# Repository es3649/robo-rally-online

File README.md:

# RoboRally Online

editing on windows now

RoboRally Online is a Typescript/robotics implementation of the RoboRally board game, by Richard Garfield and Renegade Game Studio.

One day, while playing RoboRally, I thought to myself, _"How cool would it be if the robots on the board were actual robots, and I could actually program them?"_ so I decided to make it for real.
I started with a high-school physics knowledge of electronics, then read forums, watched videos, and bothered friends until I was able to figure out how to make it work.
This repository contains a majority of the files and code needed to bring the project to life.

**Disclaimer**: This project is not affiliated with nor endorsed by Richard Garfield nor Renegade Game Studio

## Contents

* [Contents](#contents)
* [Setup Instructions](#setup-instructions)
* [Project Structure](#project-structure)
    * [Player Client](#player-client)
    * [Host Application](#host-application)
    * [Bot Drivers](#bot-drivers)
    * [Schematics](#schematics)

## Setup Instructions

This project is the fullest stack application&mdash;all it's missing is a database.
Instructions for setting up a game (assuming the code is installed, running, and the bots are assembled) can be found in [playing.md](./doc/playing.md).
More comprehensive setup instructions, including instructions for setting up the execution environment and assembling bots, are provided in [setup.md](./doc/setup.md).

## Project Structure

The project is broken into 4 main parts:

* Player Client
* Host Application
* Bot Drivers
* Schematics

### Player Client

The Player Client, contained in the `player-client` directory, is a Vue+Vite+Pinia web application which provides a web interface for playing the game

### Host Application

The host application, in the `robo-rally-host` folder, is an Electron+Vite+Vue3 desktop application written in Typescript which provides an interface for starting the game, choosing some game settings, and managing Bluetooth connections with the robots.
It also contains a express-powered and socket.io-enabled server for hosting and joining games, and for handling communication with the players.
This server serves the Player Client.

### Bot Drivers

The bot drivers, in the `bot-drivers` directory, are a series of Arduino programs, designed to control robots over a Bluetooth connection managed by the host.

### Schematics

The `schematics` folder contains PCB and CAD schematics.

The PCB schematics are created using KiCad to model the custom boards used inside each robot.
For simplicity, there is one schematic to service all bots, and thus all robot features will be supported on each PCB.
Robots which do not support a certain feature, will simply have relevant components omitted, and will not have those components supported in their drivers.

CAD schematics are created in OnShape, and contain the 3D models for the robots.
Each of these is unique.

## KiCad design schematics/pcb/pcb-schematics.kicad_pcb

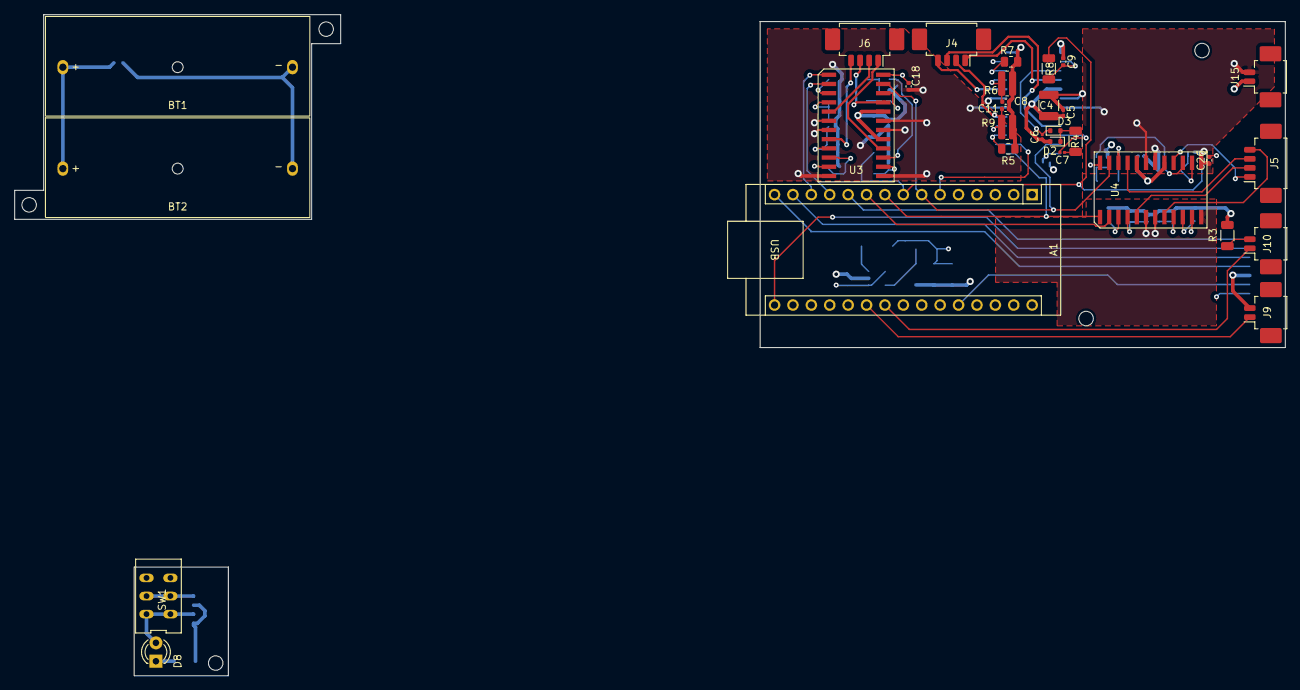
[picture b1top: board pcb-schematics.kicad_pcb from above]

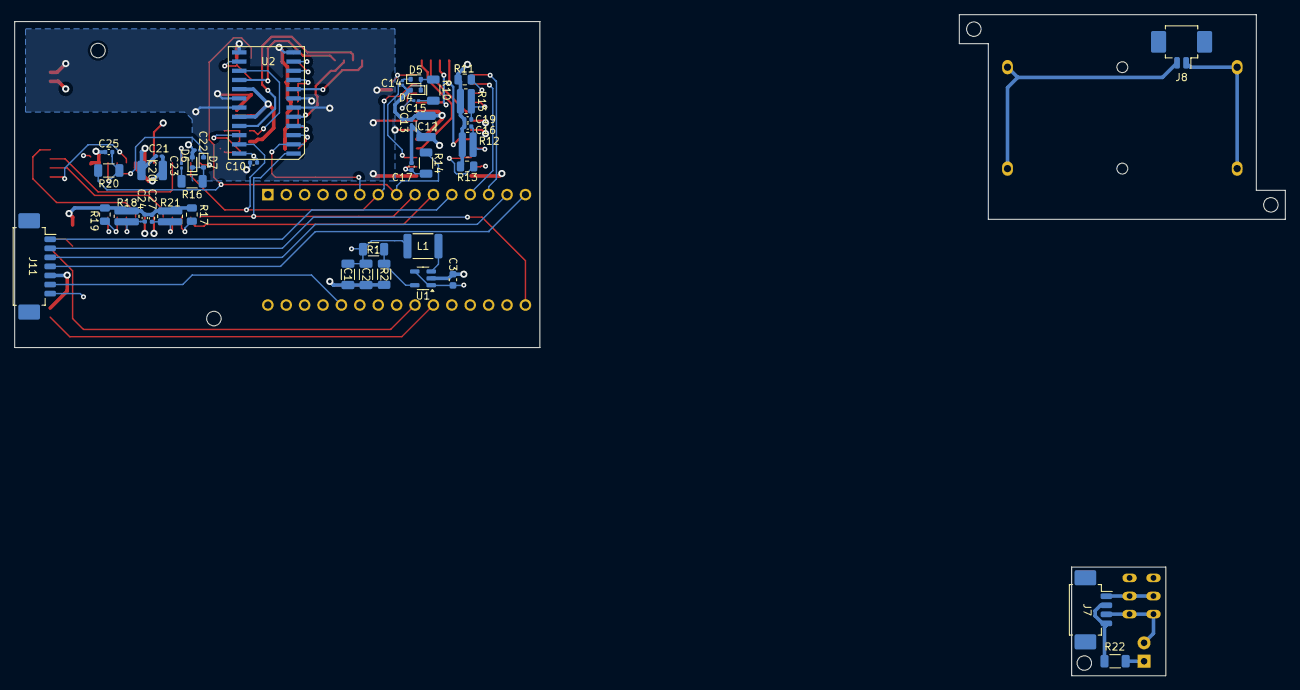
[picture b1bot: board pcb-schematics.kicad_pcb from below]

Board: 4 copper layers, 175.4 x 91.2 mm, 74 parts (43 on the bottom side), 66 nets.

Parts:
A1: Arduino_Nano_33_BLE; Arduino_Nano
BT1, BT2: Battery; Battery_clip-MPD_BHA23APC
C1, C2: 22uF; C_1206_3216Metric
C3: 4.7uF; C_0603_1608Metric
C4, C12, C20: 100uF; C_1210_3225Metric
C5, C13, C21: 0.1uF; C_0201_0603Metric_Pad0.64x0.40mm_HandSolder
C6, C14, C22: 0.22uF; C_0201_0603Metric
C7, C15, C23: 0.01uF; C_0201_0603Metric
C8, C11, C16, C19, C24, C27: 1000pF; C_0402_1005Metric
C9, C17, C25: 5600pF; C_0402_1005Metric
C10, C18, C26: 0.068uF; C_0402_1005Metric
D2, D3, D4, D5, D6, D7: 1N4148; D_SOD-523
D8: LED; LED_D3.0mm
J4, J5, J6, J7: Conn_01x04_Socket; Molex_PicoBlade_53261-0471_1x04-1MP_P1.25mm_Horizontal
J8, J9, J10, J15: Conn_01x02_Socket; Molex_PicoBlade_53261-0271_1x02-1MP_P1.25mm_Horizontal
J11: Conn_01x07_Socket; Molex_PicoBlade_53261-0771_1x07-1MP_P1.25mm_Horizontal
L1: 2.2uH; L_1812_4532Metric
R1, R8, R14, R20, R22: 100K; R_1206_3216Metric
R2: 200K; R_1206_3216Metric
R3, R4, R10, R16: 100; R_1206_3216Metric
R5, R6, R11, R12, R17, R18: 0.3; R_0805_2012Metric
R7, R9, R13, R15, R19, R21: 39K; R_0612_1632Metric
SW1: SW_DPDT_x2; SW-Slide_Diptronics-LSSA22
U1: TLV62568DBV; SOT-23-5
U2, U3, U4: L6208D; SO24_7.5x15.3mm_P1.27mm

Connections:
+12V: A1.30 (VIN), C4.2, C5.2, C6.1, C12.2, C13.2, C14.1, C20.2, C21.2, C22.1, D2.2 (A), D4.2 (A), D6.2 (A), J15.1, U2.17 (VSB), U2.20 (VSA), U3.17 (VSB), U3.20 (VSA), U4.17 (VSB), U4.20 (VSA)
/Motor Driver1/CLK: A1.13 (D10), U3.1 (CLOCK)
/Motor Driver1/CW/CCW: A1.12 (D9), U3.2 (CW/CCW)
/Motor Driver1/OUT1A: J6.2, U3.5 (OUT1A)
/Motor Driver1/OUT1B: J6.4, U3.8 (OUT1B)
/Motor Driver1/OUT2A: J6.3, U3.21 (OUT2A)
/Motor Driver1/OUT2B: J6.1, U3.16 (OUT2B)
/Motor Driver2/CW/CCW: A1.10 (D7), U4.2 (CW/CCW)
/Motor Driver2/OUT1A: J5.2, U4.5 (OUT1A)
/Motor Driver2/OUT1B: J5.4, U4.8 (OUT1B)
/Motor Driver2/OUT2A: J5.3, U4.21 (OUT2A)
/Motor Driver2/OUT2B: J5.1, U4.16 (OUT2B)
/Motor Driver/CLK: A1.9 (D6), U2.1 (CLOCK), U4.1 (CLOCK)
/Motor Driver/CW/CCW: A1.6 (D3), U2.2 (CW/CCW)
/Motor Driver/EN: A1.8 (D5), R8.2, R14.2, R20.2
/Motor Driver/OUT1A: J4.2, U2.5 (OUT1A)
/Motor Driver/OUT1B: J4.4, U2.8 (OUT1B)
/Motor Driver/OUT2A: J4.3, U2.21 (OUT2A)
/Motor Driver/OUT2B: J4.1, U2.16 (OUT2B)
/Motor Driver/RESET: A1.7 (D4), U2.23 (RESET), U3.23 (RESET), U4.23 (RESET)
/Motor Driver/VREF: C1.2, C2.2, C10.2, C18.2, C26.2, L1.1, R1.2, U2.11 (VREFB), U2.24 (VREFA), U3.11 (VREFB), U3.24 (VREFA), U4.11 (VREFB), U4.24 (VREFA)
GND: A1.4 (GND), A1.29 (GND), C1.1, C2.1, C3.2, C4.1, C5.1, C8.2, C9.1, C10.1, C11.2, C12.1, C13.1, C16.2, C17.1, C18.1, C19.2, C20.1, C21.1, C24.2, C25.1, C26.1, C27.2, J9.2, J11.5, J15.2, R2.1, R3.2, R5.1, R6.1, R7.2, R9.2, R11.1, R12.1, R13.2, R15.2, R17.1, R18.1, R19.2, R21.2, U1.2 (GND), U2.6 (GND_1), U2.7 (GND_2), U2.12 (HALF/FULL), U2.13 (CONTROL), U2.18 (GND_3), U2.19 (GND_4), U3.6 (GND_1), U3.7 (GND_2), U3.12 (HALF/FULL), U3.13 (CONTROL), U3.18 (GND_3), U3.19 (GND_4), U4.6 (GND_1), U4.7 (GND_2), U4.12 (HALF/FULL), U4.13 (CONTROL), U4.18 (GND_3), U4.19 (GND_4)
unnamed: A1.17 (3V3), C3.1, J11.7, U1.1 (EN), U1.4 (VIN)
unnamed: A1.21 (A2), J9.1
unnamed: A1.22 (A3), J10.1
unnamed: A1.26 (A7), J11.6
unnamed: A1.11 (D8), J11.1
unnamed: A1.14 (D11/MOSI), J11.3
unnamed: A1.15 (D12/MISO), J11.4
unnamed: A1.16 (D13/CLK), J11.2
unnamed: BT1.1 (+), BT2.1 (+), J8.1
unnamed: BT1.2 (-), BT2.2 (-), J8.2
unnamed: C7.1, R4.2
unnamed: C15.1, R10.2
unnamed: C23.1, R16.2
unnamed: D2.1 (K), D3.2 (A), R4.1
unnamed: C6.2, D3.1 (K), U2.15 (VBOOT)
unnamed: D4.1 (K), D5.2 (A), R10.1
unnamed: C14.2, D5.1 (K), U3.15 (VBOOT)
unnamed: D6.1 (K), D7.2 (A), R16.1
unnamed: C22.2, D7.1 (K), U4.15 (VBOOT)
unnamed: D8.2 (A), J7.3, SW1.1 (A), SW1.4 (A)
unnamed: D8.1 (K), R22.2
unnamed: J7.1, SW1.2 (B), SW1.5 (B)
unnamed: J7.2, J7.4, R22.1
unnamed: J10.2, R3.1
unnamed: R1.1, R2.2, U1.5 (FB)
unnamed: L1.2, U1.3 (SW)
unnamed: C9.2, R8.1, U2.14 (EN)
unnamed: C11.1, R9.1, U2.4 (RCA)
unnamed: C8.1, R7.1, U2.9 (RCB)
unnamed: R5.2, U2.3 (SENSE_A)
unnamed: R6.2, U2.10 (SENSE_B)
unnamed: C7.2, U2.22 (VCP)
unnamed: C17.2, R14.1, U3.14 (EN)
unnamed: C19.1, R15.1, U3.4 (RCA)
unnamed: C16.1, R13.1, U3.9 (RCB)
unnamed: R11.2, U3.3 (SENSE_A)
unnamed: R12.2, U3.10 (SENSE_B)
unnamed: C15.2, U3.22 (VCP)
unnamed: C25.2, R20.1, U4.14 (EN)
unnamed: C27.1, R21.1, U4.4 (RCA)
unnamed: C24.1, R19.1, U4.9 (RCB)
unnamed: R17.2, U4.3 (SENSE_A)
unnamed: R18.2, U4.10 (SENSE_B)
unnamed: C23.2, U4.22 (VCP)

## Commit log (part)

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2024-06-18 initial commit
    project configured
2024-06-21 adds other init files
2024-06-21 added join and host views
2024-06-22 adds game server structure
2024-06-25 rename client files
2024-06-26 build out some of the server
2024-06-26 adds robot images
2024-06-28 finished host server rough draft
2024-06-29 restructured shared imports
2024-06-30 added connection store; setup dev env
2024-07-02 wire up host.vue
2024-07-03 started game_state store
    added programming cards
2024-07-10 started building UI and game state
2024-07-12 adds more game components and UI
2024-07-14 draggable cards work
    only one card per register
2024-07-23 added the desktop application
    server was moved into the desktop application
2024-07-24 added vue3 to electron app
2024-08-06 added board data models and board data files
2024-08-06 config updates
2024-08-06 added some UI for the renderer
2024-08-06 added robot data
2024-08-11 loads of stuff
    it compiles and runs
2024-08-14 Data model work for movements and boards
2024-08-16 adds board loader and renderer
2024-08-16 small spacing update
2024-08-16 added Windows setup instructions
2024-08-21 html server works now
2024-08-22 socket connection is active
2024-09-18 adds lots of communication structure
    especially client to server and server to main
2024-10-02 commit before rewrite
    main-server communication needs rewrite
2024-10-14 changed orientation of turning conveyors
    outgoing direction is always forward
2024-10-17 added unit tests
2024-10-17 adds hardware files
    also updates a test
2024-10-17 pushing all code updates
2024-10-18 adds conv_LR and board_loader tests
2024-10-18 add test data boards
2024-10-20 added tests and fixed bugs
2024-10-22 updating tests
2024-10-24 bug fixes and more tests added
2024-10-27 added tests and board element activation
2024-11-12 finally might have the pushers right
2024-11-22 code update before ActionFrame rewrite
2024-11-22 schematic and driver rewrite
2024-11-28 update algos to use movement frame
2024-11-28 more frame rewriting
2024-11-29 final frame updates
2024-12-23 PusherForest rewrite, adds move_processors
2024-12-24 mostly finished with game core
2024-12-24 updated imports
2024-12-25 tests compile
2024-12-26 most tests working
    failing on a new desired bahavior for
    wall collisions
2024-12-26 all graph.ts tests passing
2024-12-27 all tests passing
2025-01-19 adds test sketches
2025-01-19 manager rewrite to state machine
2025-01-19 adds spawn tiles
2025-01-21 polished and tested (most of) PlayerManager
2025-01-30 bluetooth draft & docs update
2025-02-05 added game state and executor
    first test passing
2025-02-06 added a second test for game_state
    ficed a bug allowing some actors to glitch
    through walls when pushed
2025-02-07 initial draft
    missing status LED, state changes
    BLE-related compile errors
2025-02-08 axel driver rough draft finished
    desparately needs testing
2025-02-08 missed compilation errors
2025-02-08 fixes issues in game_state tests
2025-02-25 player client goes through lobby
2025-02-25 small gamemanager updates for better api
2025-02-26 adds BLE test and test schematics
2025-02-26 adds license
2025-02-26 add source svgs for cards
2025-03-04 variable movement/renames, pipeline development
2025-03-05 added progression to upgrade and session refresh
2025-03-08 added comms for GetAction and GetInput
2025-03-18 reorganize shared files and update imports
    player client and host build ok
    tests failing
2025-03-22 moved server handlers to different files
2025-03-28 adds lots of html/js structure for the client
2025-03-28 move handlers to separate files
    adds more communication functionality
2025-03-30 client UI structure/function complete
2025-04-29 KiCad schematics at manufacture
2025-06-06 AvtionWindow superceded by shared/GameEvent
2025-06-17 started mucking about with CSS
2025-06-19 added more styles
    Mobile is starting to look good
2025-06-20 polished Mobile UI
2025-07-01 using windows
2025-07-04 added game-over page
2025-07-06 update cards to remove artifacts
2025-07-30 added client game over screen
2025-07-30 added winner end condition check
2025-07-31 updated messaging types between main and server
    all tests passing
2025-07-31 minor client UI updates
2025-07-31 major console UI update
2025-08-23 update package version to remove vulnerabilities
2025-08-26 updated to get server running on pi
2025-09-13 add port forwarding scripts for macOS
2025-09-13 adds events and BT updates
2025-09-17 fixes syntax errors in client
2025-09-17 Bluetooth piptline fixes
    BT now connects, but can't get service
2025-09-21 added player removal from host
2025-09-23 moved notifier class defns to separate file
2025-09-23 client is able to recover game state within lobby
